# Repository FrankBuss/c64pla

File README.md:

Project webpage: https://frank-buss.de/c64/pla/index.html

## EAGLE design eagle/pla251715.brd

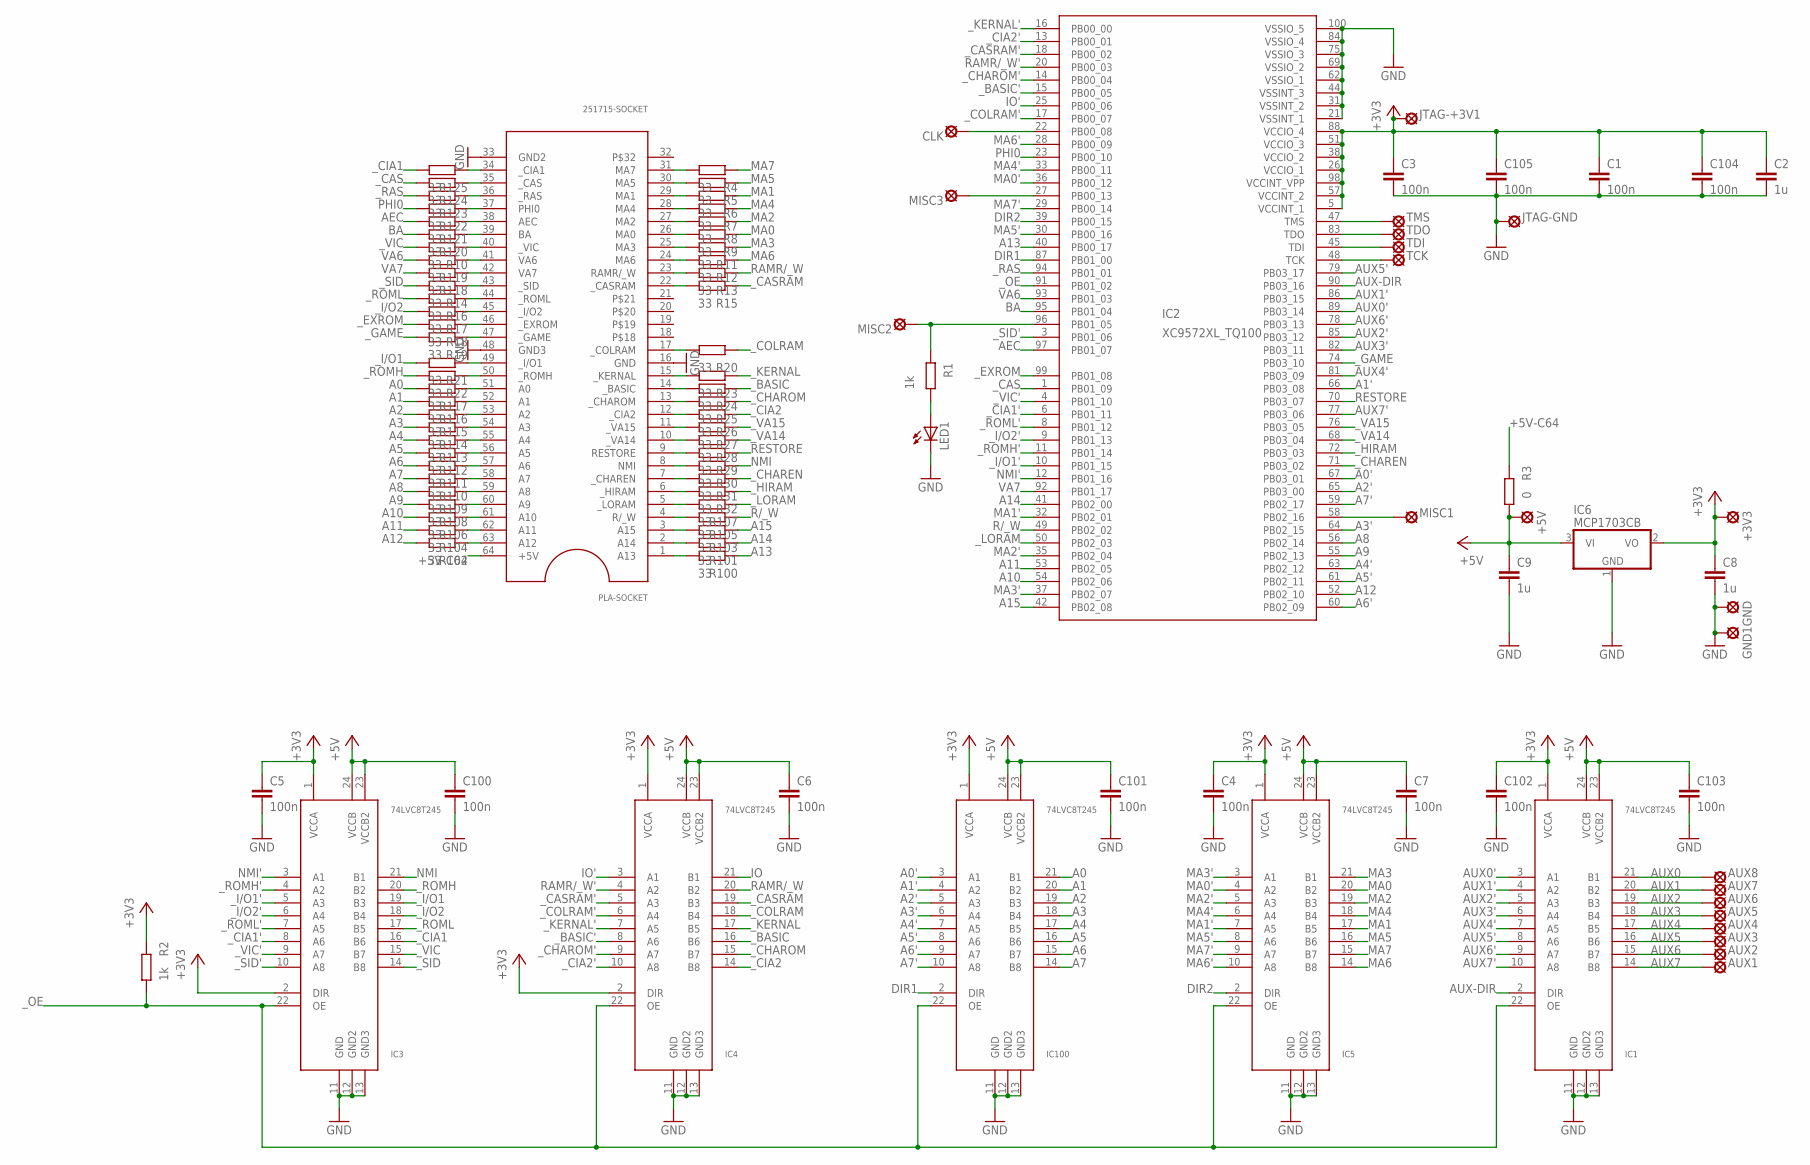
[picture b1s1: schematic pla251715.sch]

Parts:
+3V3, +5V: LSP10
AUX1, AUX2, AUX3, AUX4, AUX5, AUX6, AUX7, AUX8: LSP10
C1, C3, C4, C5, C6, C7, C100, C101, C102, C103, C104, C105: 100n; C0603
C2, C8, C9: 1u; C1210
CLK: LSP10
GND, GND1: LSP10
IC1, IC3, IC4, IC5, IC100: 74LVC8T245; TSSOP24
IC2: XC9572XL_TQ100; TQ100
IC6: MCP1703CB; SOT23
JTAG-+3V1: LSP10
JTAG-GND: LSP10
LED1: LED5MM
MISC1, MISC2, MISC3: LSP10
PLA-SOCKET: 251715-SOCKET; 64-SPDIP
R1, R2: 1k; R0805
R3: 0; R0805
R4, R5, R6, R7, R8, R9, R10, R11, R12, R13, R14, R15, R16, R17, R18, R19, R20, R21, R22, R23, R24, R25, R26, R27, R28, R29, R30, R31, R32, R100, R101, R102, R103, R104, R105, R106, R107, R108, R109, R110, R111, R112, R113, R114, R115, R116, R117, R118, R119, R120, R121, R122, R123, R124, R125: 33; R0402
TCK: LSP10
TDI: LSP10
TDO: LSP10
TMS: LSP10

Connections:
+3V3: +3V3.MP, C1.1, C2.1, C3.1, C4.1, C5.1, C8.1, C102.1, C104.1, C105.1, IC1.1 (VCCA), IC2.5 (VCCINT_1), IC2.26 (VCCIO_1), IC2.38 (VCCIO_2), IC2.51 (VCCIO_3), IC2.57 (VCCINT_2), IC2.88 (VCCIO_4), IC2.98 (VCCINT_VPP), IC3.1 (VCCA), IC3.2 (DIR), IC4.1 (VCCA), IC4.2 (DIR), IC5.1 (VCCA), IC6.2 (VO), IC100.1 (VCCA), JTAG-+3V1.MP, R2.1
+5V: +5V.MP, C6.1, C7.1, C9.1, C100.1, C101.1, C103.1, IC1.23 (VCCB2), IC1.24 (VCCB), IC3.23 (VCCB2), IC3.24 (VCCB), IC4.23 (VCCB2), IC4.24 (VCCB), IC5.23 (VCCB2), IC5.24 (VCCB), IC6.3 (VI), IC100.23 (VCCB2), IC100.24 (VCCB), R3.2
+5V-C64: PLA-SOCKET.64 (+5V), R3.1
A0: IC100.21 (B1), R117.2
A0': IC2.67 (PB03_01), IC100.3 (A1)
A1: IC100.20 (B2), R116.2
A1': IC2.66 (PB03_08), IC100.4 (A2)
A2: IC100.19 (B3), R115.2
A2': IC2.65 (PB03_00), IC100.5 (A3)
A3: IC100.18 (B4), R114.2
A3': IC2.64 (PB02_15), IC100.6 (A4)
A4: IC100.17 (B5), R113.2
A4': IC2.63 (PB02_12), IC100.7 (A5)
A5: IC100.16 (B6), R112.2
A5': IC2.61 (PB02_11), IC100.8 (A6)
A6: IC100.15 (B7), R111.2
A6': IC2.60 (PB02_09), IC100.9 (A7)
A7: IC100.14 (B8), R110.2
A7': IC2.59 (PB02_17), IC100.10 (A8)
A8: IC2.56 (PB02_14), R109.2
A9: IC2.55 (PB02_13), R108.2
A10: IC2.54 (PB02_06), R106.2
A11: IC2.53 (PB02_05), R104.2
A12: IC2.52 (PB02_10), R102.2
A13: IC2.40 (PB00_17), R100.1
A14: IC2.41 (PB02_00), R101.1
A15: IC2.42 (PB02_08), R103.1
AEC: IC2.97 (PB01_07), R121.2
AUX0: AUX8.MP, IC1.21 (B1)
AUX0': IC1.3 (A1), IC2.89 (PB03_14)
AUX1: AUX7.MP, IC1.20 (B2)
AUX1': IC1.4 (A2), IC2.86 (PB03_15)
AUX2: AUX6.MP, IC1.19 (B3)
AUX2': IC1.5 (A3), IC2.85 (PB03_12)
AUX3: AUX5.MP, IC1.18 (B4)
AUX3': IC1.6 (A4), IC2.82 (PB03_11)
AUX4: AUX4.MP, IC1.17 (B5)
AUX4': IC1.7 (A5), IC2.81 (PB03_09)
AUX5: AUX3.MP, IC1.16 (B6)
AUX5': IC1.8 (A6), IC2.79 (PB03_17)
AUX6: AUX2.MP, IC1.15 (B7)
AUX6': IC1.9 (A7), IC2.78 (PB03_13)
AUX7: AUX1.MP, IC1.14 (B8)
AUX7': IC1.10 (A8), IC2.77 (PB03_06)
AUX-DIR: IC1.2 (DIR), IC2.90 (PB03_16)
BA: IC2.95 (PB01_04), R120.2
DIR1: IC2.87 (PB01_00), IC100.2 (DIR)
DIR2: IC2.39 (PB00_15), IC5.2 (DIR)
GND: C1.2, C2.2, C3.2, C4.2, C5.2, C6.2, C7.2, C8.2, C9.2, C100.2, C101.2, C102.2, C103.2, C104.2, C105.2, GND.MP, GND1.MP, IC1.11 (GND), IC1.12 (GND2), IC1.13 (GND3), IC2.21 (VSSINT_1), IC2.31 (VSSINT_2), IC2.44 (VSSINT_3), IC2.62 (VSSIO_1), IC2.69 (VSSIO_2), IC2.75 (VSSIO_3), IC2.84 (VSSIO_4), IC2.100 (VSSIO_5), IC3.11 (GND), IC3.12 (GND2), IC3.13 (GND3), IC4.11 (GND), IC4.12 (GND2), IC4.13 (GND3), IC5.11 (GND), IC5.12 (GND2), IC5.13 (GND3), IC6.1 (GND), IC100.11 (GND), IC100.12 (GND2), IC100.13 (GND3), JTAG-GND.MP, LED1.K (C), PLA-SOCKET.16 (GND), PLA-SOCKET.33 (GND2), PLA-SOCKET.48 (GND3)
IO: IC4.21 (B1)
IO': IC2.25 (PB00_06), IC4.3 (A1)
MA0: IC5.20 (B2), R9.1
MA0': IC2.36 (PB00_12), IC5.4 (A2)
MA1: IC5.17 (B5), R6.1
MA1': IC2.32 (PB02_01), IC5.7 (A5)
MA2: IC5.19 (B3), R8.1
MA2': IC2.35 (PB02_04), IC5.5 (A3)
MA3: IC5.21 (B1), R11.1
MA3': IC2.37 (PB02_07), IC5.3 (A1)
MA4: IC5.18 (B4), R7.1
MA4': IC2.33 (PB00_11), IC5.6 (A4)
MA5: IC5.16 (B6), R5.1
MA5': IC2.30 (PB00_16), IC5.8 (A6)
MA6: IC5.14 (B8), R12.1
MA6': IC2.28 (PB00_09), IC5.10 (A8)
MA7: IC5.15 (B7), R4.1
MA7': IC2.29 (PB00_14), IC5.9 (A7)
unnamed: IC2.96 (PB01_05), MISC2.MP, R1.1
unnamed: IC2.58 (PB02_16), MISC1.MP
unnamed: IC2.27 (PB00_13), MISC3.MP
unnamed: LED1.A, R1.2
unnamed: CLK.MP, IC2.22 (PB00_08)
unnamed: PLA-SOCKET.17 (_COLRAM), R20.2
unnamed: PLA-SOCKET.31 (MA7), R4.2
unnamed: PLA-SOCKET.30 (MA5), R5.2
unnamed: PLA-SOCKET.15 (_KERNAL), R23.2
unnamed: PLA-SOCKET.29 (MA1), R6.2
unnamed: PLA-SOCKET.28 (MA4), R7.2
unnamed: PLA-SOCKET.27 (MA2), R8.2
unnamed: PLA-SOCKET.26 (MA0), R9.2
unnamed: PLA-SOCKET.25 (MA3), R11.2
unnamed: PLA-SOCKET.24 (MA6), R12.2
unnamed: PLA-SOCKET.23 (RAMR/_W), R13.2
unnamed: PLA-SOCKET.22 (_CASRAM), R15.2
unnamed: PLA-SOCKET.14 (_BASIC), R24.2
unnamed: PLA-SOCKET.13 (_CHAROM), R25.2
unnamed: PLA-SOCKET.12 (_CIA2), R26.2
unnamed: PLA-SOCKET.11 (_VA15), R27.2
unnamed: PLA-SOCKET.10 (_VA14), R28.2
unnamed: PLA-SOCKET.9 (RESTORE), R29.2
unnamed: PLA-SOCKET.8 (NMI), R30.2
unnamed: PLA-SOCKET.7 (_CHAREN), R31.2
unnamed: PLA-SOCKET.6 (_HIRAM), R32.2
unnamed: PLA-SOCKET.5 (_LORAM), R107.2
unnamed: PLA-SOCKET.4 (R/_W), R105.2
unnamed: PLA-SOCKET.3 (A15), R103.2
unnamed: PLA-SOCKET.2 (A14), R101.2
unnamed: PLA-SOCKET.1 (A13), R100.2
unnamed: PLA-SOCKET.63 (A12), R102.1
unnamed: PLA-SOCKET.62 (A11), R104.1
unnamed: PLA-SOCKET.61 (A10), R106.1
unnamed: PLA-SOCKET.60 (A9), R108.1
unnamed: PLA-SOCKET.59 (A8), R109.1
unnamed: PLA-SOCKET.58 (A7), R110.1
unnamed: PLA-SOCKET.57 (A6), R111.1
unnamed: PLA-SOCKET.56 (A5), R112.1
unnamed: PLA-SOCKET.55 (A4), R113.1
unnamed: PLA-SOCKET.54 (A3), R114.1
unnamed: PLA-SOCKET.53 (A2), R115.1
unnamed: PLA-SOCKET.52 (A1), R116.1
unnamed: PLA-SOCKET.51 (A0), R117.1
unnamed: PLA-SOCKET.50 (_ROMH), R22.1
unnamed: PLA-SOCKET.49 (_I/O1), R21.1
unnamed: PLA-SOCKET.47 (_GAME), R19.1
unnamed: PLA-SOCKET.46 (_EXROM), R18.1
unnamed: PLA-SOCKET.45 (_I/O2), R17.1
unnamed: PLA-SOCKET.44 (_ROML), R16.1
unnamed: PLA-SOCKET.43 (_SID), R14.1
unnamed: PLA-SOCKET.42 (VA7), R118.1
unnamed: PLA-SOCKET.41 (VA6), R119.1
unnamed: PLA-SOCKET.40 (_VIC), R10.1
unnamed: PLA-SOCKET.39 (BA), R120.1
unnamed: PLA-SOCKET.38 (AEC), R121.1
unnamed: PLA-SOCKET.37 (PHI0), R122.1
unnamed: PLA-SOCKET.36 (_RAS), R123.1
unnamed: PLA-SOCKET.35 (_CAS), R124.1
unnamed: PLA-SOCKET.34 (_CIA1), R125.1
NMI: IC3.21 (B1), R30.1
NMI': IC2.12 (PB01_16), IC3.3 (A1)
PHI0: IC2.23 (PB00_10), R122.2
R/_W: IC2.49 (PB02_02), R105.1
RAMR/_W: IC4.20 (B2), R13.1
RAMR/_W': IC2.20 (PB00_03), IC4.4 (A2)
RESTORE: IC2.70 (PB03_07), R29.1
TCK: IC2.48 (TCK), TCK.MP
TDI: IC2.45 (TDI), TDI.MP
TDO: IC2.83 (TDO), TDO.MP
TMS: IC2.47 (TMS), TMS.MP
VA6: IC2.93 (PB01_03), R119.2
VA7: IC2.92 (PB01_17), R118.2
_BASIC: IC4.16 (B6), R24.1
_BASIC': IC2.15 (PB00_05), IC4.8 (A6)
_CAS: IC2.1 (PB01_09), R124.2
_CASRAM: IC4.19 (B3), R15.1
_CASRAM': IC2.18 (PB00_02), IC4.5 (A3)
_CHAREN: IC2.71 (PB03_02), R31.1
_CHAROM: IC4.15 (B7), R25.1
_CHAROM': IC2.14 (PB00_04), IC4.9 (A7)
_CIA1: IC3.16 (B6), R125.2
_CIA1': IC2.6 (PB01_11), IC3.8 (A6)
_CIA2: IC4.14 (B8), R26.1
_CIA2': IC2.13 (PB00_01), IC4.10 (A8)
_COLRAM: IC4.18 (B4), R20.1
_COLRAM': IC2.17 (PB00_07), IC4.6 (A4)
_EXROM: IC2.99 (PB01_08), R18.2
_GAME: IC2.74 (PB03_10), R19.2
_HIRAM: IC2.72 (PB03_03), R32.1
_I/O1: IC3.19 (B3), R21.2
_I/O1': IC2.10 (PB01_15), IC3.5 (A3)
_I/O2: IC3.18 (B4), R17.2
_I/O2': IC2.9 (PB01_13), IC3.6 (A4)
_KERNAL: IC4.17 (B5), R23.1
_KERNAL': IC2.16 (PB00_00), IC4.7 (A5)
_LORAM: IC2.50 (PB02_03), R107.1
_OE: IC1.22 (OE), IC2.91 (PB01_02), IC3.22 (OE), IC4.22 (OE), IC5.22 (OE), IC100.22 (OE), R2.2
_RAS: IC2.94 (PB01_01), R123.2
_ROMH: IC3.20 (B2), R22.2
_ROMH': IC2.11 (PB01_14), IC3.4 (A2)
_ROML: IC3.17 (B5), R16.2
_ROML': IC2.8 (PB01_12), IC3.7 (A5)
_SID: IC3.14 (B8), R14.2
_SID': IC2.3 (PB01_06), IC3.10 (A8)
_VA14: IC2.68 (PB03_04), R28.1
_VA15: IC2.76 (PB03_05), R27.1
_VIC: IC3.15 (B7), R10.2
_VIC': IC2.4 (PB01_10), IC3.9 (A7)

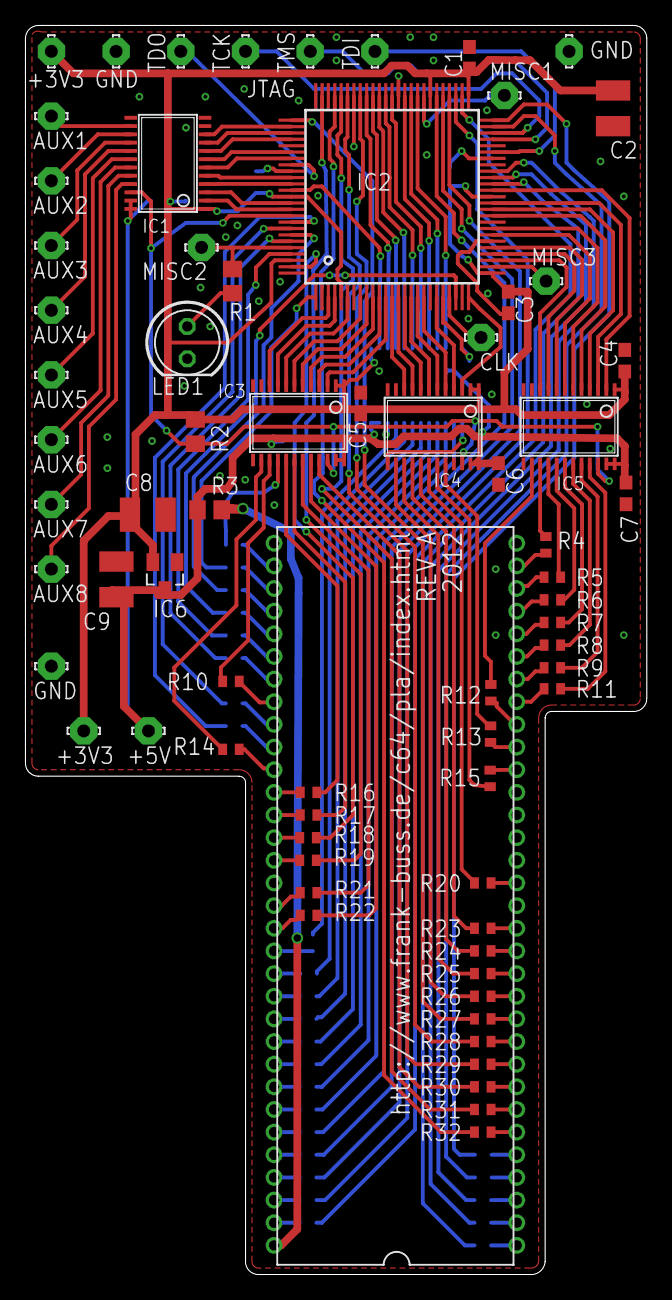
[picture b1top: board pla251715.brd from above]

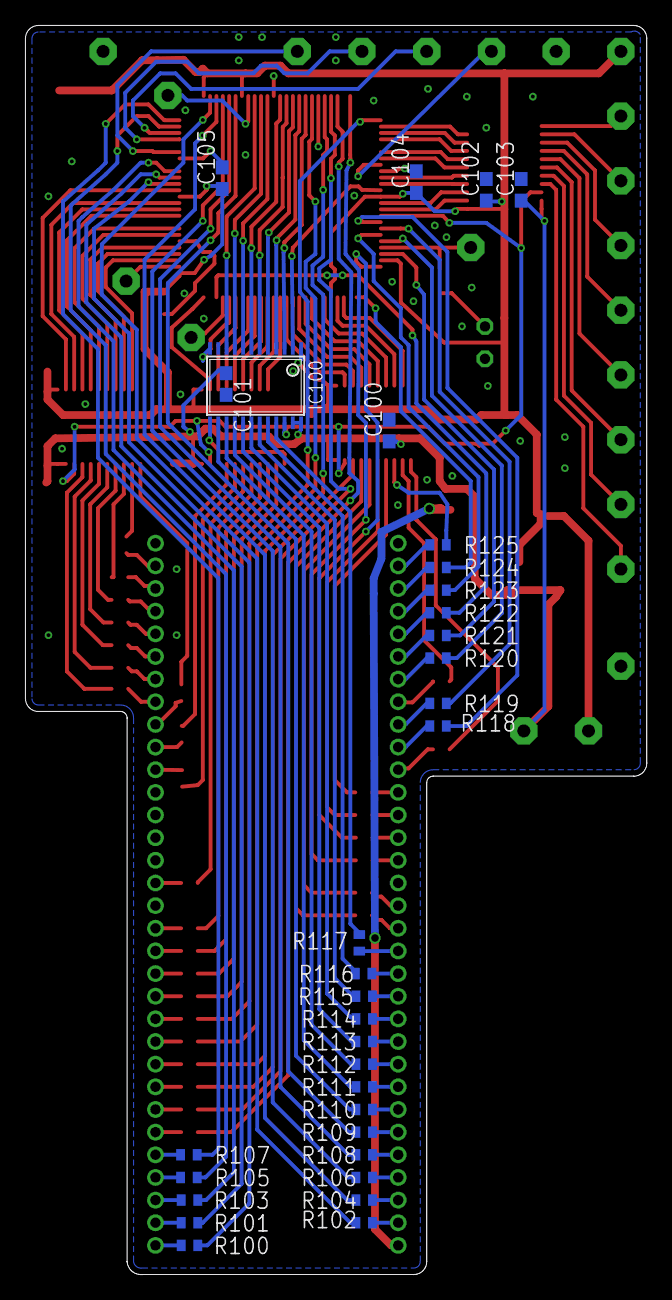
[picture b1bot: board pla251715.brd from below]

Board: 2 copper layers, 48.8 x 98.0 mm, 104 parts (33 on the bottom side), 175 nets.

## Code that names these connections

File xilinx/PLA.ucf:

NET "clk" PERIOD = 100.0ns ;
NET "kernal" LOC = "16" ;
NET "cia2" LOC = "13" ;
NET "casram" LOC = "18" ;
NET "ramrw" LOC = "20" ;
NET "charom" LOC = "14" ;
NET "basic" LOC = "15" ;
NET "io" LOC = "25" ;
NET "colram" LOC = "17" ;
NET "clk" LOC = "22" ;
NET "ma<6>" LOC = "28" ;
NET "phi0" LOC = "23" ;
NET "ma<4>" LOC = "33" ;
NET "ma<0>" LOC = "36" ;
NET "misc3" LOC = "27" ;
NET "ma<7>" LOC = "29" ;
NET "dir2" LOC = "39" ;
NET "ma<5>" LOC = "30" ;
NET "a<13>" LOC = "40" ;
NET "dir1" LOC = "87" ;
NET "ras" LOC = "94" ;
NET "oe" LOC = "91" ;
NET "va6" LOC = "93" ;
NET "ba" LOC = "95" ;
NET "misc2" LOC = "96" ;
NET "sid" LOC = "3" ;
NET "aec" LOC = "97" ;
NET "exrom" LOC = "99" ;
NET "cas" LOC = "1" ;
NET "vic" LOC = "4" ;
NET "cia1" LOC = "6" ;
NET "roml" LOC = "8" ;
NET "io2" LOC = "9" ;
NET "romh" LOC = "11" ;
NET "io1" LOC = "10" ;
NET "nmi" LOC = "12" ;
NET "va7" LOC = "92" ;
NET "a<14>" LOC = "41" ;
NET "ma<1>" LOC = "32" ;
NET "rw" LOC = "49" ;
NET "loram" LOC = "50" ;
NET "ma<2>" LOC = "35" ;
NET "a<11>" LOC = "53" ;
NET "a<10>" LOC = "54" ;
NET "ma<3>" LOC = "37" ;
NET "a<15>" LOC = "42" ;
NET "a<6>" LOC = "60" ;
NET "a<12>" LOC = "52" ;
NET "a<5>" LOC = "61" ;
NET "a<4>" LOC = "63" ;
NET "a<9>" LOC = "55" ;
NET "a<8>" LOC = "56" ;
NET "a<3>" LOC = "64" ;
NET "misc1" LOC = "58" ;
NET "a<7>" LOC = "59" ;
NET "a<2>" LOC = "65" ;
NET "a<0>" LOC = "67" ;
NET "charen" LOC = "71" ;
NET "hiram" LOC = "72" ;
NET "va14" LOC = "68" ;
NET "va15" LOC = "76" ;
NET "aux<7>" LOC = "77" ;
NET "restore" LOC = "70" ;
NET "a<1>" LOC = "66" ;
NET "aux<4>" LOC = "81" ;
NET "game" LOC = "74" ;
NET "aux<3>" LOC = "82" ;
NET "aux<2>" LOC = "85" ;
NET "aux<6>" LOC = "78" ;
NET "aux<0>" LOC = "89" ;
NET "aux<1>" LOC = "86" ;
NET "aux_dir" LOC = "90" ;
NET "aux<5>" LOC = "79" ;

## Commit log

2012-11-17 removed redundant "component" declaration
2012-11-24 ucf file and simple LED blinking example added
2012-12-15 Added a new file describing the additional TTL chips present in the 'c' version that are included in the new PLA for that version.
2012-12-15 Fixed the compile problems.
2012-12-16 Heavy re-factoring to make use of the existing c64pla7 as a base for this 251715 version.
2012-12-16 Added the PLA.ucf to the project and edited it where needed to accommodate the changes.
2012-12-16 Re-wrote and fixed the 74139 2->4 demux signal definitions.
2012-12-16 Added a needed connection for ioBuffer and 'io' output pin.
2012-12-16 Added NMI signal and cleaned up some unnecessery comments.
2012-12-16 Added definitions for output directions and voltage level shifter controls. Also added a few directives to get rid of a few warnings.
2012-12-16 added the 74139 chip and testbench
2012-12-17 Added the 74257 chip and modified the main PLA file to use it.
2013-01-12 Added the 74258 chip and modified the main PLA file to use it
2013-01-12 Added the 74373 chip and modified the main PLA file to use it.
2013-01-12 The modified project files that were forgotten from the previous commit.
2013-01-12 Fixed the broken 74373 implementation.
2013-01-12 Altered so, that if output is enabled even though the latch enabling is no longer valid, the last state is still being outputted.
2013-01-13 Moved the 74373 and 74258 files from xilinx/ to vhdl/
2013-01-13 Re-factored the 74258 to use the multiplexer entity instead of it's own inverted multiplexer to reduce duplicate code.
2013-01-13 Fixed the 74373 output drive condition. Now should go to 'Z' only when neither condition applies.
2013-01-13 Added the inclusion of 'gn' signal to enable the multiplexers.
2013-01-13 Added 'Z' condition to the multiplexer. Sets output ('y') to 'Z' is 'gn' is '1'.
2013-01-13 Minor file management. Renamed a few files and removed an obsoleted file.
2013-01-13 Updated project files.
2013-01-13 Added instances of the '373, '257 and '258 chips from chip1.pdf
2013-01-13 Compile error fixes.
2013-01-13 Fix in the inversion logic.
2013-01-13 Set 'dir1' and 'dir2' to proper values instead of temporary ones.
2013-01-19 fixing some errors and adding a programming file
2013-01-25 first working version
2013-01-26 restoring the gates version, with the AEC bugfix
2013-01-27 Small fixes to the logic against the main-branch version.
2013-01-31 Testbench for 74258 multiplexer.
2013-01-31 Altered project files.
2013-01-31 Added more helpful logging and fixed the functiontable.
2013-01-31 Fixed the multiplexer. The conditions on when Y = A and then Y = B were the wrong way around.
2013-06-19 adding GR/_W signal and fixing testbench
2013-06-25 Applied the fix for grw signal from the main branch and the fix for the testbench also.
